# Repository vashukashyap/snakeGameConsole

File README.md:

# Snake Game Console
Hi, this is my project "Snake Game Console"
## Configurations
IDE : `PlatformIO`  
Microcontroller  : `ESP8266`  
Peripheral : `oled 0.96 Inch` , `Push Button` , `3.3v lithium-ion Battery` , `TDA2822 IC` , `100uF-50V Polar Capacitor` , `Speaker`  
Library : `Adafruit GFX Library` , `Adafruit SSD1306`

## PINS CONNECTIONS
  D7-->Sound_Output  
  D6-->Left_Button  
  D5-->Right_Button  
  G-->Display_GND / TDA2822_GND  
  3V-->Display_VCC / TDA2822_VCC  
  D4-->Display_SCK  
  D3-->Display_SDA  
  D2-->Down_Button  
  D1-->Up_Button  

## Project SETUP
  You can view hardware folder file in KICAD and firmware folder file in VSCODE just make sure you had installed the PlatformIO extension in the VSCode.
  On opening Firmware folder in vscode platformIO automatically detect its project and do the setup automatically.
  #### Build
  Click on the Build Button which look like this `✓`
  ### Flash
  Click on the Flash Button which look like this `→`

## Photos

# Enclosure for my project is Here!...
https://a360.co/49LJf49

😊.....

## Videos

https://github.com/user-attachments/assets/daafca41-82c4-4b3c-846a-305e06488c9d

https://github.com/user-attachments/assets/c5736373-c8b9-427d-92ab-c476b570b2c2

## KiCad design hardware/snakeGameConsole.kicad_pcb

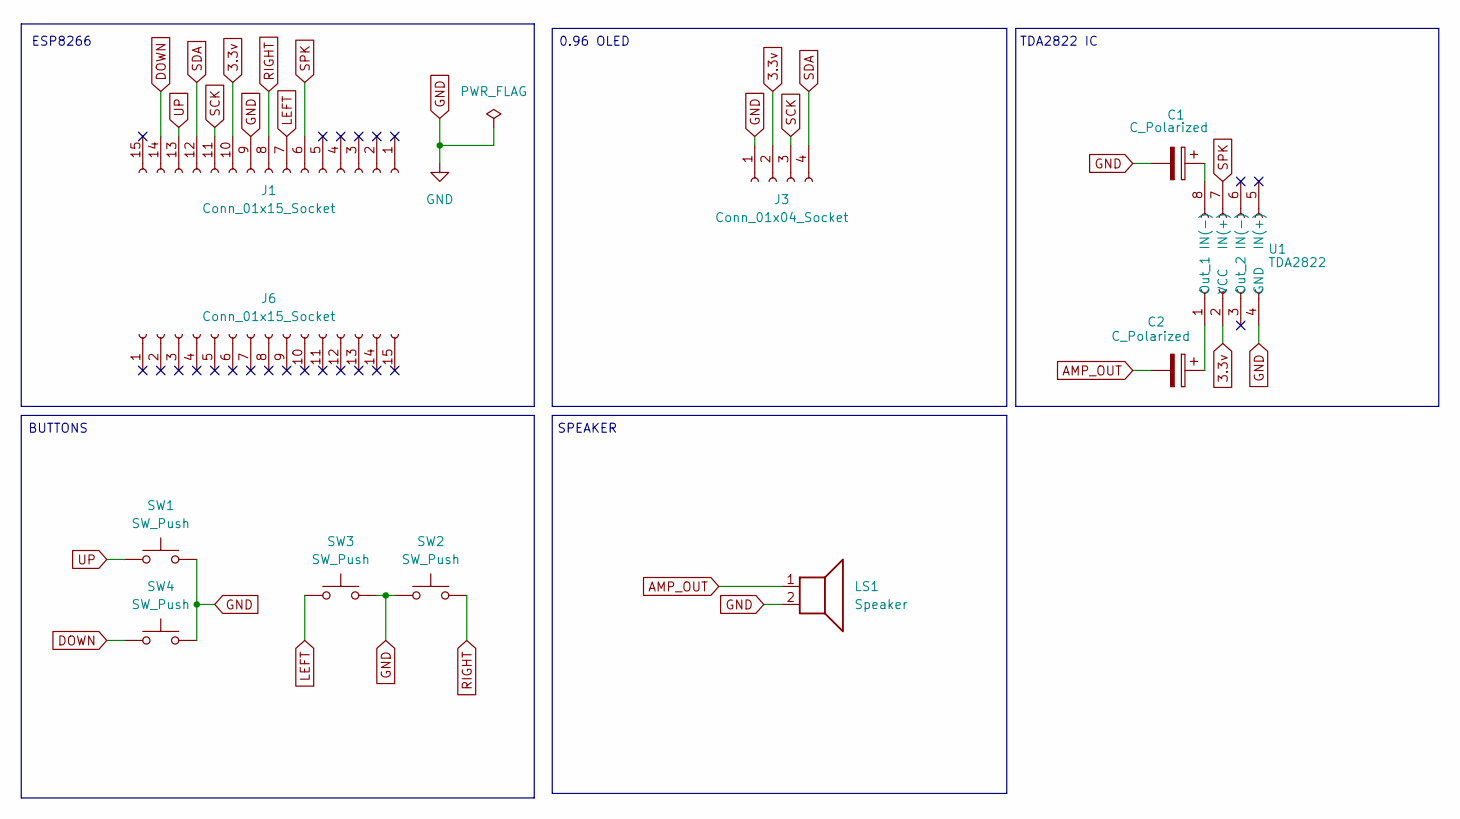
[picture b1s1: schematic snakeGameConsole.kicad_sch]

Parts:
C1, C2: C_Polarized; CP_Radial_D4.0mm_P1.50mm
J1, J6: Conn_01x15_Socket; PinSocket_1x15_P2.00mm_Vertical
J3: Conn_01x04_Socket; PinSocket_1x04_P2.00mm_Vertical
LS1: Speaker; Buzzer_12x9.5RM7.6
SW1, SW2, SW3, SW4: SW_Push; SW_PUSH_1P1T_6x3.5mm_H5.0_APEM_MJTP1250
U1: TDA2822; DIP-8_W7.62mm

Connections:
3.3v: J1.10, J3.2, U1.2 (VCC)
AMP_OUT: C2.2, LS1.1
DOWN: J1.14, SW4.1
GND: C1.2, J1.9, J3.1, LS1.2, SW1.2, SW2.1, SW3.2, SW4.2, U1.4 (GND)
LEFT: J1.7, SW3.1
unnamed: C1.1, U1.8 (IN(-))
unnamed: C2.1, U1.1 (Out_1)
RIGHT: J1.8, SW2.2
SCK: J1.11, J3.3
SDA: J1.12, J3.4
SPK: J1.6, U1.7 (IN(+))
UP: J1.13, SW1.1

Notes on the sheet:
ESP8266
SPEAKER
TDA2822 IC
0.96 OLED
BUTTONS

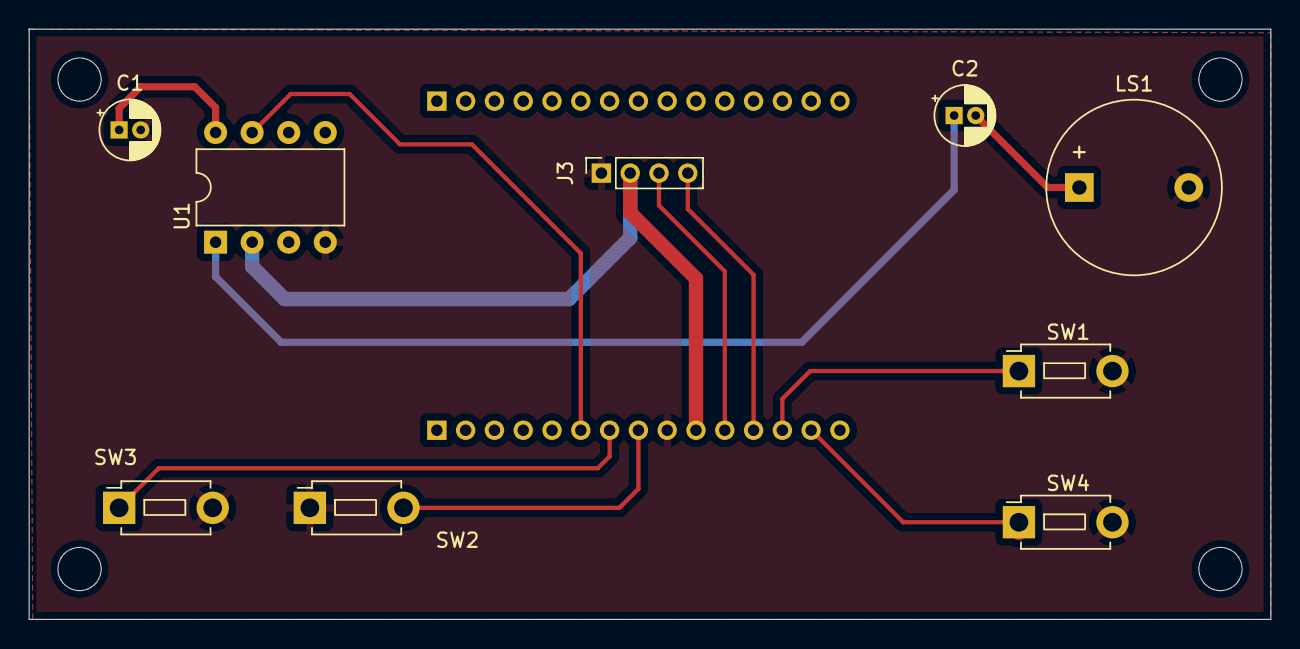
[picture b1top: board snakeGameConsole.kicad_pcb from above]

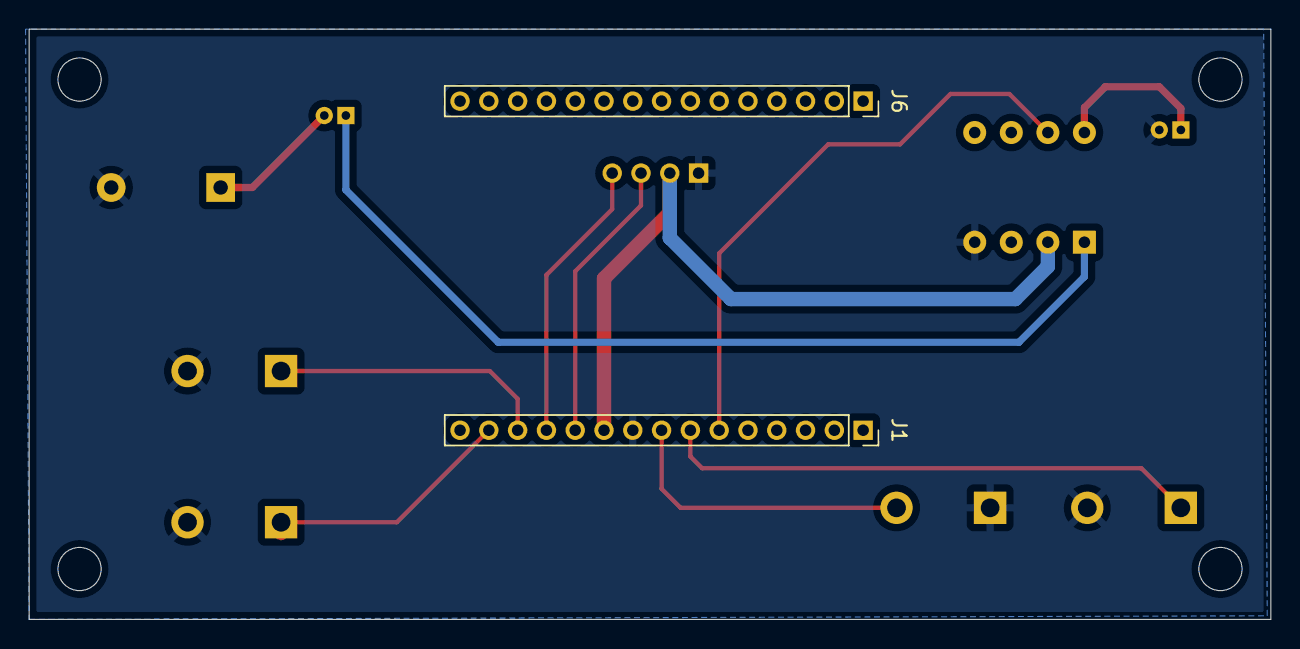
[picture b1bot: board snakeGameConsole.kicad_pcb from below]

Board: 2 copper layers, 86.2 x 41.0 mm, 11 parts (2 on the bottom side), 12 nets.

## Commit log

2024-12-15 project-finished
2024-12-15 added git ignored
2024-12-15 fixing a file error
2024-12-15 fixed file error
2024-12-21 Update README.md added Enclosure link
